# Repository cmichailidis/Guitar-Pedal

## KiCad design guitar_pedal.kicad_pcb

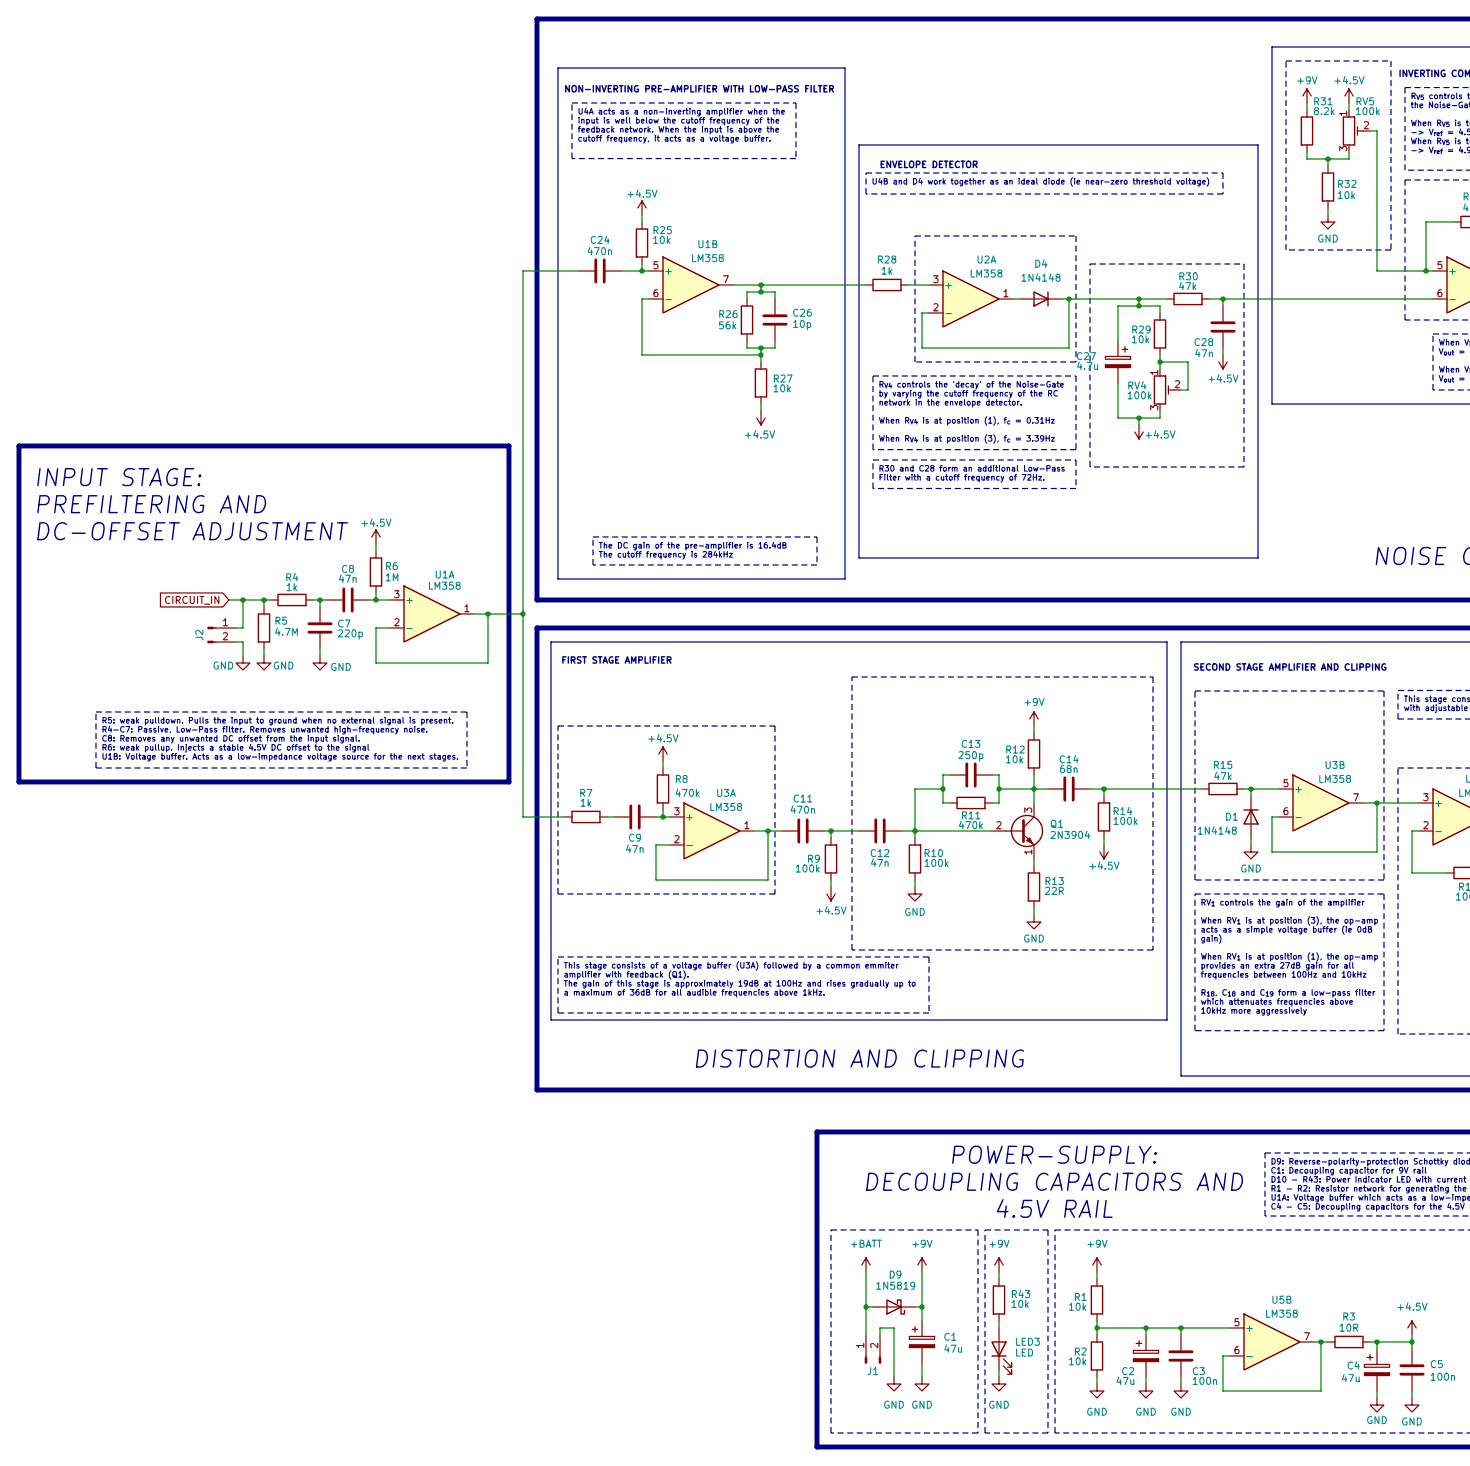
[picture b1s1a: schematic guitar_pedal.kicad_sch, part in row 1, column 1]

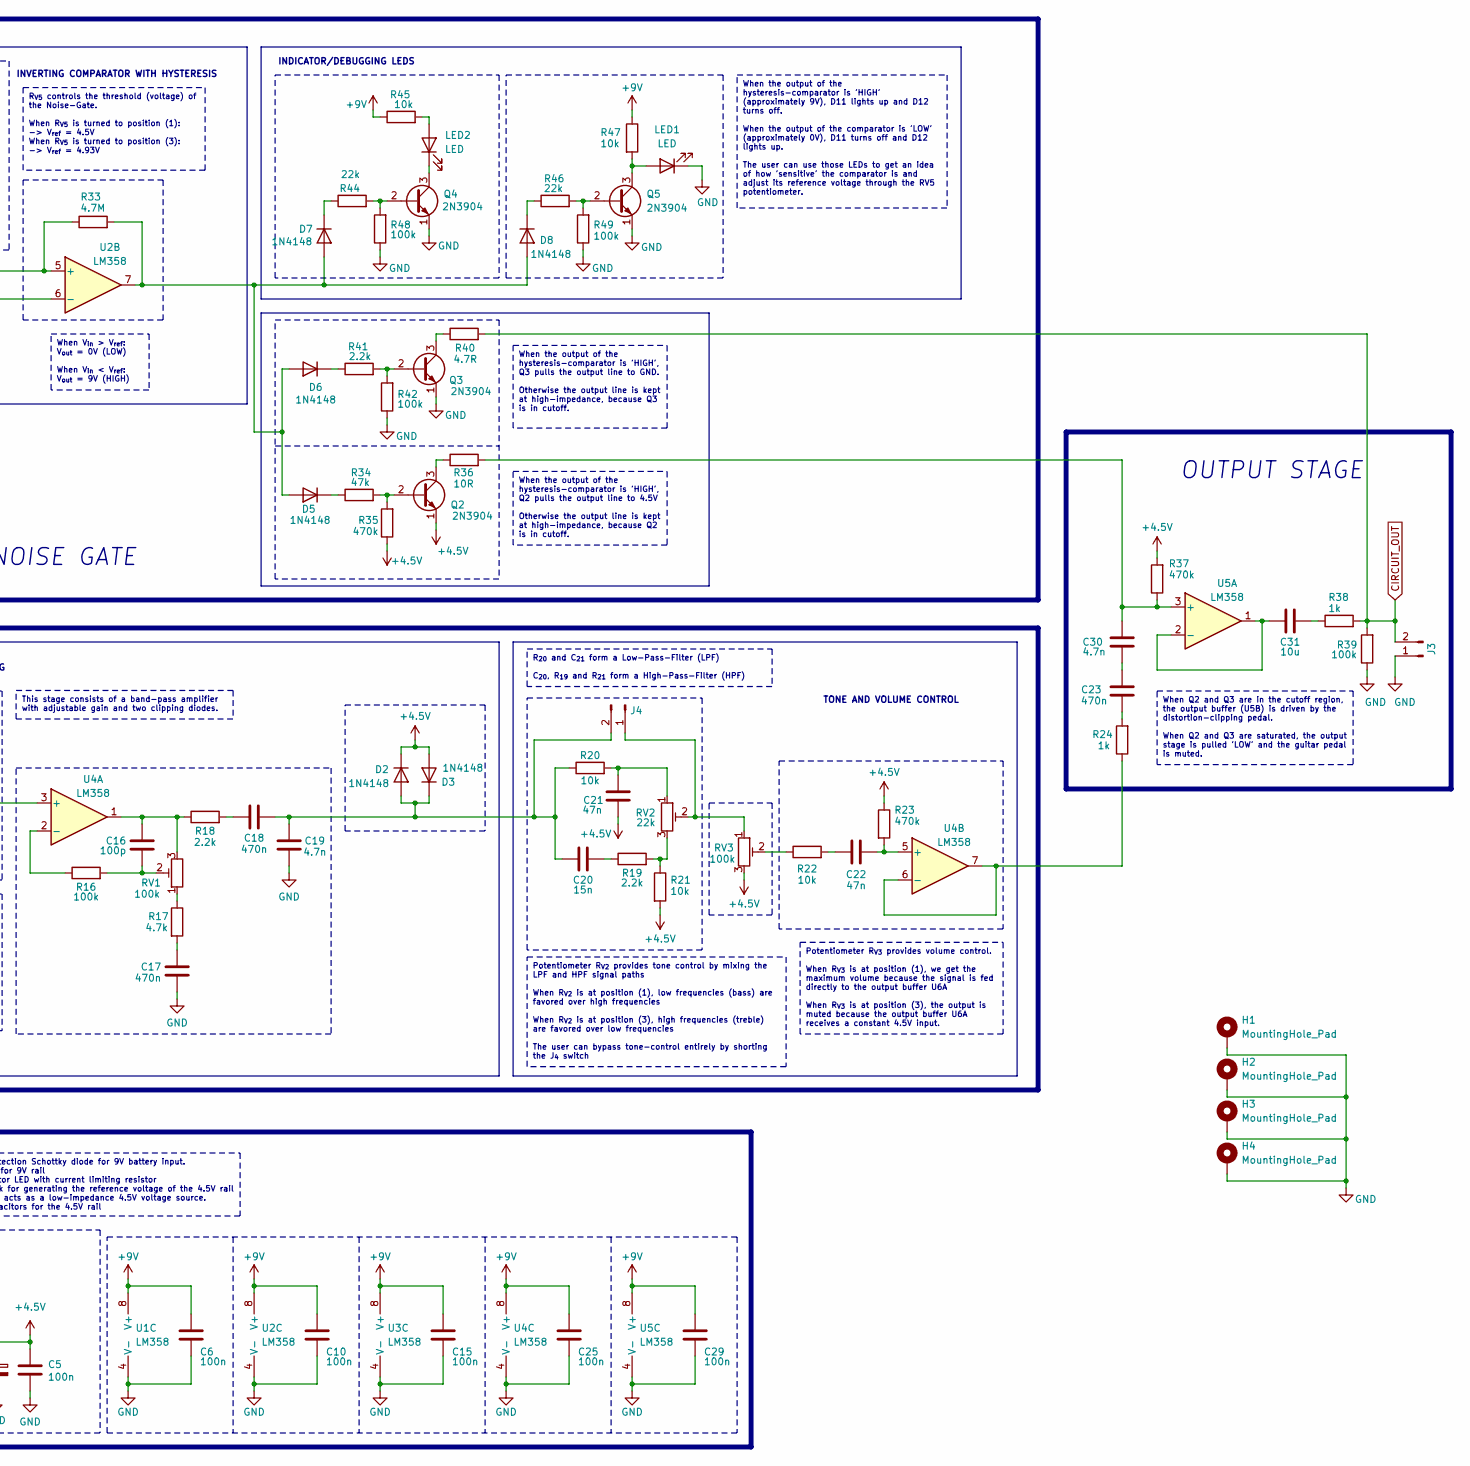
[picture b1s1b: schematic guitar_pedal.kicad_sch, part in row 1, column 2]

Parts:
C1, C2, C4: 47u; CP_Radial_D6.3mm_P2.50mm
C3, C5, C6, C10, C15, C25, C29: 100n; C_Rect_L7.2mm_W2.5mm_P5.00mm_FKS2_FKP2_MKS2_MKP2
C7: 220p; C_Disc_D6.0mm_W2.5mm_P5.00mm
C8, C9, C12, C21, C22, C28: 47n; C_Rect_L7.2mm_W2.5mm_P5.00mm_FKS2_FKP2_MKS2_MKP2
C11, C17, C18, C23, C24: 470n; C_Rect_L7.2mm_W3.5mm_P5.00mm_FKS2_FKP2_MKS2_MKP2
C13: 250p; C_Disc_D6.0mm_W2.5mm_P5.00mm
C14: 68n; C_Rect_L7.2mm_W2.5mm_P5.00mm_FKS2_FKP2_MKS2_MKP2
C16: 100p; C_Disc_D6.0mm_W2.5mm_P5.00mm
C19, C30: 4.7n; C_Rect_L7.2mm_W2.5mm_P5.00mm_FKS2_FKP2_MKS2_MKP2
C20: 15n; C_Rect_L7.2mm_W2.5mm_P5.00mm_FKS2_FKP2_MKS2_MKP2
C26: 10p; C_Disc_D6.0mm_W2.5mm_P5.00mm
C27: 4.7u; CP_Radial_D5.0mm_P2.50mm
C31: 10u; C_Disc_D6.0mm_W2.5mm_P5.00mm
D1, D2, D3, D4, D5, D6, D7, D8: 1N4148; D_DO-35_SOD27_P7.62mm_Horizontal
D9: 1N5819; D_DO-41_SOD81_P10.16mm_Horizontal
H1, H2, H3, H4: MountingHole_Pad; MountingHole_3.2mm_M3_DIN965_Pad
J1, J2, J3, J4: Conn_01x02_Pin; PinHeader_1x02_P2.54mm_Vertical
LED1, LED2, LED3: LED; PinHeader_1x02_P2.54mm_Vertical
Q1, Q2, Q3, Q4, Q5: 2N3904; TO-92_Inline
R1, R2, R12, R20, R21, R22, R25, R27, R29, R32, R43, R45, R47: 10k; R_Axial_DIN0207_L6.3mm_D2.5mm_P7.62mm_Horizontal
R3, R36: 10R; R_Axial_DIN0207_L6.3mm_D2.5mm_P7.62mm_Horizontal
R4, R7, R24, R28, R38: 1k; R_Axial_DIN0207_L6.3mm_D2.5mm_P7.62mm_Horizontal
R5, R33: 4.7M; R_Axial_DIN0207_L6.3mm_D2.5mm_P7.62mm_Horizontal
R6: 1M; R_Axial_DIN0207_L6.3mm_D2.5mm_P7.62mm_Horizontal
R8, R11, R23, R35, R37: 470k; R_Axial_DIN0207_L6.3mm_D2.5mm_P7.62mm_Horizontal
R9, R10, R14, R16, R39, R42, R48, R49: 100k; R_Axial_DIN0207_L6.3mm_D2.5mm_P7.62mm_Horizontal
R13: 22R; R_Axial_DIN0207_L6.3mm_D2.5mm_P7.62mm_Horizontal
R15, R30, R34: 47k; R_Axial_DIN0207_L6.3mm_D2.5mm_P7.62mm_Horizontal
R17: 4.7k; R_Axial_DIN0207_L6.3mm_D2.5mm_P7.62mm_Horizontal
R18, R19, R41: 2.2k; R_Axial_DIN0207_L6.3mm_D2.5mm_P7.62mm_Horizontal
R26: 56k; R_Axial_DIN0207_L6.3mm_D2.5mm_P7.62mm_Horizontal
R31: 8.2k; R_Axial_DIN0207_L6.3mm_D2.5mm_P7.62mm_Horizontal
R40: 4.7R; R_Axial_DIN0207_L6.3mm_D2.5mm_P7.62mm_Horizontal
R44, R46: 22k; R_Axial_DIN0207_L6.3mm_D2.5mm_P7.62mm_Horizontal
RV1, RV3, RV4, RV5: 100k; PinHeader_1x03_P2.54mm_Vertical
RV2: 22k; PinHeader_1x03_P2.54mm_Vertical
U1, U2, U3, U4, U5: LM358; DIP-8_W7.62mm

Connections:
+4.5V: C4.1, C5.2, C21.1, C27.2, C28.1, D2.1 (K), D3.2 (A), Q2.1 (E), R3.2, R6.1, R8.1, R9.1, R14.1, R21.2, R23.1, R25.1, R27.2, R35.1, R37.2, RV3.3, RV4.3, RV5.1
+9V: C1.1, C6.2, C10.2, C15.2, C25.2, C29.2, D9.1 (K), R1.1, R12.1, R31.1, R43.1, R45.1, R47.1, U1.8 (V+), U2.8 (V+), U3.8 (V+), U4.8 (V+), U5.8 (V+)
+BATT: D9.2 (A), J1.1
CIRCUIT_IN: J2.1, R4.1, R5.1
CIRCUIT_OUT: J3.2, R38.2, R39.2, R40.2
GND: C1.2, C2.2, C3.1, C4.2, C5.1, C6.1, C7.1, C10.1, C15.1, C17.1, C19.1, C25.1, C29.1, D1.2 (A), H1.1 (1_1), H2.1 (1_1), H3.1 (1_1), H4.1 (1_1), J1.2, J2.2, J3.1, LED1.1 (K), LED3.1 (K), Q3.1 (E), Q4.1 (E), Q5.1 (E), R2.2, R5.2, R10.1, R13.2, R32.2, R39.1, R42.1, R48.1, R49.1, U1.4 (V-), U2.4 (V-), U3.4 (V-), U4.4 (V-), U5.4 (V-)
unnamed: C7.2, C8.1, R4.2
unnamed: C9.1, R7.2
unnamed: C11.2, C12.2, R9.2
unnamed: C14.2, R14.2, R15.1
unnamed: C16.1, R16.2, RV1.2
unnamed: C16.2, R18.1, RV1.3, U4.1
unnamed: C17.2, R17.2
unnamed: C18.1, R18.2
unnamed: C20.2, R19.1
unnamed: C21.2, R20.2, RV2.1
unnamed: C22.1, R22.2
unnamed: C23.1, R24.2
unnamed: C23.2, C30.1
unnamed: C26.2, R26.1, R28.1, U1.7
unnamed: C31.2, R38.1
unnamed: D1.1 (K), R15.2, U3.5 (+)
unnamed: C18.2, C19.2, C20.1, D2.2 (A), D3.1 (K), J4.2, R20.1
unnamed: D4.2 (A), U2.1
unnamed: C27.1, D4.1 (K), R29.1, R30.1, U2.2 (-)
unnamed: D5.2 (A), D6.2 (A), D7.2 (A), D8.2 (A), R33.2, U2.7
unnamed: D5.1 (K), R34.1
unnamed: D6.1 (K), R41.1
unnamed: D7.1 (K), R44.1
unnamed: D8.1 (K), R46.1
unnamed: J4.1, RV2.2, RV3.1
unnamed: LED1.2 (A), Q5.3 (C), R47.2
unnamed: LED2.2 (A), R45.2
unnamed: LED2.1 (K), Q4.3 (C)
unnamed: LED3.2 (A), R43.2
unnamed: C12.1, C13.1, Q1.2 (B), R10.2, R11.1
unnamed: C13.2, C14.1, Q1.3 (C), R11.2, R12.2
unnamed: Q1.1 (E), R13.1
unnamed: Q2.2 (B), R34.2, R35.2
unnamed: Q2.3 (C), R36.1
unnamed: Q3.2 (B), R41.2, R42.2
unnamed: Q3.3 (C), R40.1
unnamed: Q4.2 (B), R44.2, R48.2
unnamed: Q5.2 (B), R46.2, R49.2
unnamed: R17.1, RV1.1
unnamed: R19.2, R21.1, RV2.3
unnamed: R22.1, RV3.2
unnamed: R29.2, RV4.1, RV4.2
unnamed: R31.2, R32.1, RV5.3
unnamed: C8.2, R6.2, U1.3 (+)
unnamed: C24.1, R7.1, U1.1, U1.2 (-)
unnamed: C24.2, R25.2, U1.5 (+)
unnamed: C26.1, R26.2, R27.1, U1.6 (-)
unnamed: R28.2, U2.3 (+)
unnamed: R33.1, RV5.2, U2.5 (+)
unnamed: C28.2, R30.2, U2.6 (-)
unnamed: C9.2, R8.2, U3.3 (+)
unnamed: C11.1, U3.1, U3.2 (-)
unnamed: U3.6 (-), U3.7, U4.3 (+)
unnamed: R16.1, U4.2 (-)
unnamed: C22.2, R23.2, U4.5 (+)
unnamed: R24.1, U4.6 (-), U4.7
unnamed: C30.2, R36.2, R37.1, U5.3 (+)
unnamed: C31.1, U5.1, U5.2 (-)
unnamed: C2.1, C3.2, R1.2, R2.1, U5.5 (+)
unnamed: R3.1, U5.6 (-), U5.7

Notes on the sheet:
SECOND STAGE AMPLIFIER AND CLIPPING
POWER-SUPPLY: DECOUPLING CAPACITORS AND 4.5V RAIL
INPUT STAGE: PREFILTERING AND DC-OFFSET ADJUSTMENT
NON-INVERTING PRE-AMPLIFIER WITH LOW-PASS FILTER
NOISE GATE
INVERTING COMPARATOR WITH HYSTERESIS
ENVELOPE DETECTOR
INDICATOR/DEBUGGING LEDS
DISTORTION AND CLIPPING
TONE AND VOLUME CONTROL
OUTPUT STAGE
FIRST STAGE AMPLIFIER
This stage consists of a voltage buffer (U3A) followed by a common emmiter amplifier with feedback (Q1). The gain of this stage is approximately 19dB at 100Hz and rises gradually up to a maximum of 36dB for all audible frequencies above 1kHz.
D9: Reverse-polarity-protection Schottky diode for 9V battery input. C1: Decoupling capacitor for 9V rail D10 - R43: Power Indicator LED with current limiting resistor R1 - R2: Resistor network for generating the reference voltage of the 4.5V rail U1A: Voltage buffer which acts as a low-impedance 4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
Potentiometer R_{V2} provides tone control by mixing the LPF and HPF signal paths When R_{V2} is at position (1), low frequencies (bass) are favored over high frequencies When R_{V2} is at position (3), high frequencies (treble) are favored over low frequencies The user can bypass tone-control enti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
When V_{in} > V_{ref}: V_{out} = 0V (LOW) When V_{in} < V_{ref}: V_{out} = 9V (HIGH)
The DC gain of the pre-amplifier is 16.4dB The cutoff frequency is 284kHz
RV_{1} controls the gain of the amplifier When RV_{1} is at position (3), the op-amp acts as a simple voltage buffer (ie 0dB gain) When RV_{1} is at position (1), the op-amp provides an extra 27dB gain for all frequencies between 100Hz and 10kHz R_{18}, C_{18} and C_{19} form a low-pass filter whic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
When the output of the hysteresis-comparator is 'HIGH', Q3 pulls the output line to GND. Otherwise the output line is kept at high-impedance, because Q3 is in cutoff.
U4B and D4 work together as an ideal diode (ie near-zero threshold voltage)
R5: weak pulldown. Pulls the input to ground when no external signal is present. R4-C7: Passive, Low-Pass filter. Removes unwanted high-frequency noise. C8: Removes any unwanted DC offset from the input signal. R6: weak pullup. Injects a stable 4.5V DC offset to the signal U1B: Voltage buffer. Acts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
R_{V5} controls the threshold (voltage) of the Noise-Gate. When R_{V5} is turned to position (1): -> V_{ref} = 4.5V When R_{V5} is turned to position (3): -> V_{ref} = 4.93V
When the output of the hysteresis-comparator is 'HIGH' (approximately 9V), D11 lights up and D12 turns off. When the output of the comparator is 'LOW' (approximately 0V), D11 turns off and D12 lights up. The user can use those LEDs to get an idea of how 'sensitive' the comparator is and adjust its 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
This stage consists of a band-pass amplifier with adjustable gain and two clipping diodes.
When the output of the hysteresis-comparator is 'HIGH', Q2 pulls the output line to 4.5V Otherwise the output line is kept at high-impedance, because Q2 is in cutoff.
R30 and C28 form an additional Low-Pass Filter with a cutoff frequency of 72Hz.
R_{20} and C_{21} form a Low-Pass-Filter (LPF) C_{20}, R_{19} and R_{21} form a High-Pass-Filter (HPF)
When Q2 and Q3 are in the cutoff region, the output buffer (U5B) is driven by the distortion-clipping pedal. When Q2 and Q3 are saturated, the output stage is pulled 'LOW' and the guitar pedal is muted.
R_{V4} controls the 'decay' of the Noise-Gate by varying the cutoff frequency of the RC network in the envelope detector. When R_{V4} is at position (1), f_{c} = 0.31Hz When R_{V4} is at position (3), f_{c} = 3.39Hz
Potentiometer R_{V3} provides volume control. When R_{V3} is at position (1), we get the maximum volume because the signal is fed directly to the output buffer U6A When R_{V3} is at position (3), the output is muted because the output buffer U6A receives a constant 4.5V input.
U4A acts as a non-inverting amplifier when the input is well below the cutoff frequency of the feedback network. When the input is above the cutoff frequency, it acts as a voltage buffer.

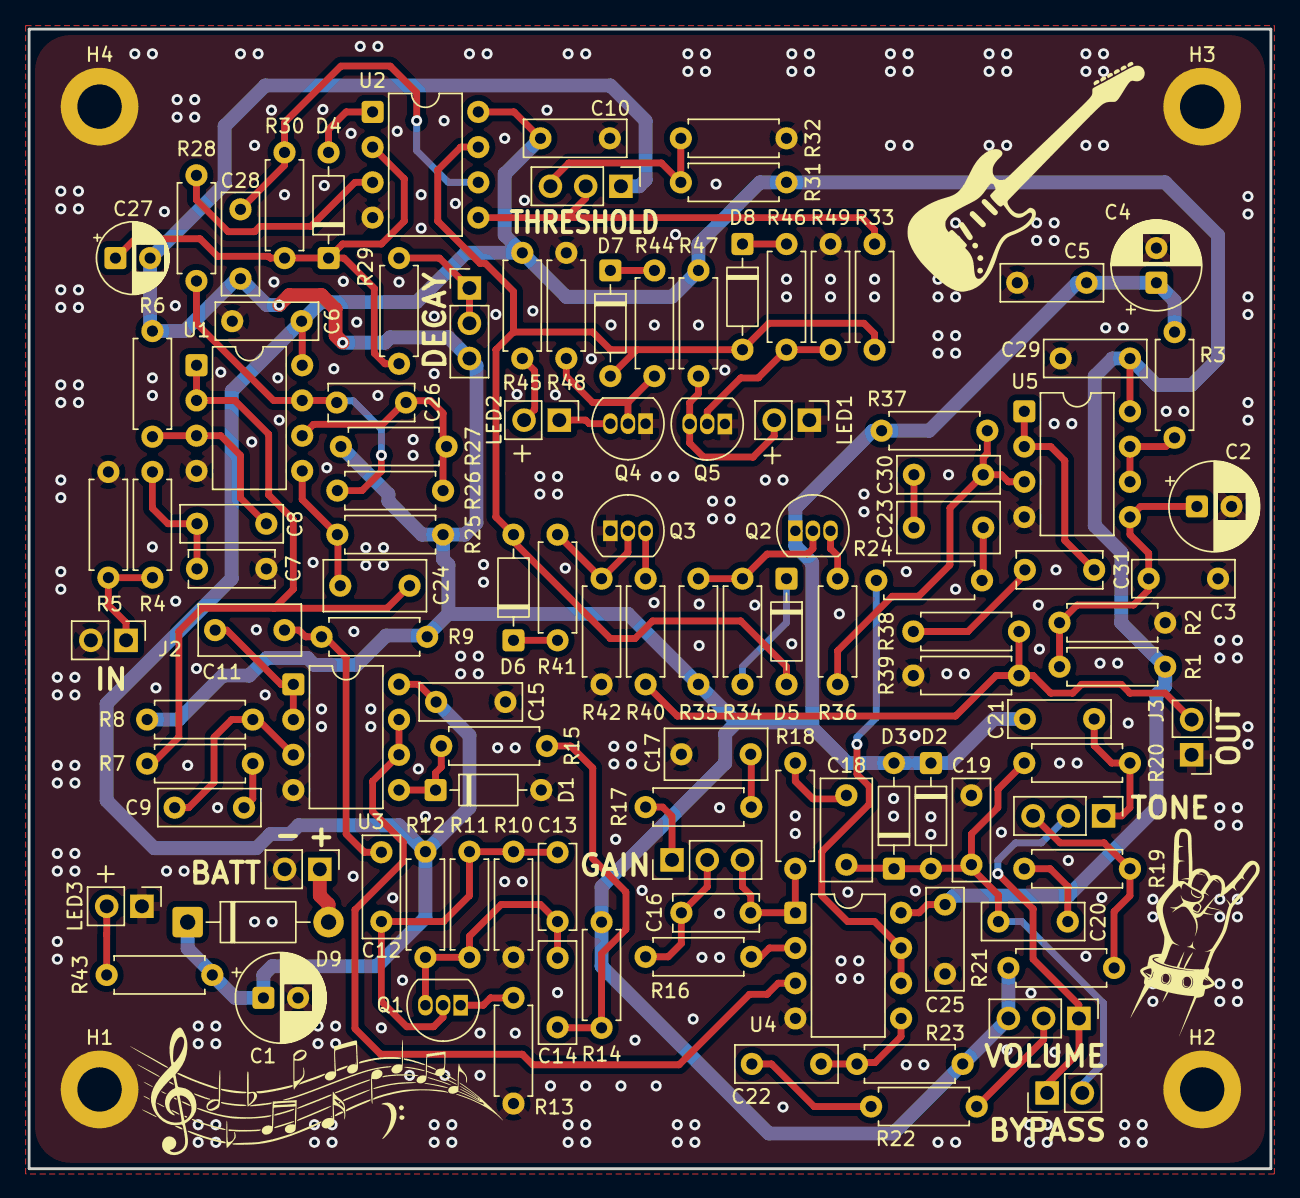
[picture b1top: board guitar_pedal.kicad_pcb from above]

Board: 2 copper layers, 89.5 x 82.2 mm, 115 parts (0 on the bottom side), 66 nets.

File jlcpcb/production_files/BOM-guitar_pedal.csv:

Comment,Designator,Footprint,LCSC,Quantity
4.7R,R40,R_Axial_DIN0207_L6.3mm_D2.5mm_P7.62mm_Horizontal,,1
47n,C21,C_Rect_L7.2mm_W2.5mm_P5.00mm_FKS2_FKP2_MKS2_MKP2,,1
2.2k,R19,R_Axial_DIN0207_L6.3mm_D2.5mm_P7.62mm_Horizontal,,1
470n,C17,C_Rect_L7.2mm_W3.5mm_P5.00mm_FKS2_FKP2_MKS2_MKP2,,1
100p,C16,C_Disc_D6.0mm_W2.5mm_P5.00mm,,1
470k,R11,R_Axial_DIN0207_L6.3mm_D2.5mm_P7.62mm_Horizontal,,1
470k,R37,R_Axial_DIN0207_L6.3mm_D2.5mm_P7.62mm_Horizontal,,1
2N3904,Q1,TO-92_Inline,,1
1N4148,D6,D_DO-35_SOD27_P7.62mm_Horizontal,,1
100n,C6,C_Rect_L7.2mm_W2.5mm_P5.00mm_FKS2_FKP2_MKS2_MKP2,,1
2.2k,R41,R_Axial_DIN0207_L6.3mm_D2.5mm_P7.62mm_Horizontal,,1
10k,R32,R_Axial_DIN0207_L6.3mm_D2.5mm_P7.62mm_Horizontal,,1
470k,R35,R_Axial_DIN0207_L6.3mm_D2.5mm_P7.62mm_Horizontal,,1
470n,C18,C_Rect_L7.2mm_W3.5mm_P5.00mm_FKS2_FKP2_MKS2_MKP2,,1
8.2k,R31,R_Axial_DIN0207_L6.3mm_D2.5mm_P7.62mm_Horizontal,,1
2.2k,R43,R_Axial_DIN0207_L6.3mm_D2.5mm_P7.62mm_Horizontal,,1
470n,C11,C_Rect_L7.2mm_W3.5mm_P5.00mm_FKS2_FKP2_MKS2_MKP2,,1
1M,R6,R_Axial_DIN0207_L6.3mm_D2.5mm_P7.62mm_Horizontal,,1
2N3904,Q5,TO-92_Inline,,1
1k,R24,R_Axial_DIN0207_L6.3mm_D2.5mm_P7.62mm_Horizontal,,1
Conn_01x02_Pin,J1,PinHeader_1x02_P2.54mm_Vertical,,1
47n,C8,C_Rect_L7.2mm_W2.5mm_P5.00mm_FKS2_FKP2_MKS2_MKP2,,1
47u,C2,CP_Radial_D6.3mm_P2.50mm,,1
2N3904,Q3,TO-92_Inline,,1
470k,R23,R_Axial_DIN0207_L6.3mm_D2.5mm_P7.62mm_Horizontal,,1
4.7M,R33,R_Axial_DIN0207_L6.3mm_D2.5mm_P7.62mm_Horizontal,,1
1k,R4,R_Axial_DIN0207_L6.3mm_D2.5mm_P7.62mm_Horizontal,,1
100R,R36,R_Axial_DIN0207_L6.3mm_D2.5mm_P7.62mm_Horizontal,,1
100k,R48,R_Axial_DIN0207_L6.3mm_D2.5mm_P7.62mm_Horizontal,,1
22k,R46,R_Axial_DIN0207_L6.3mm_D2.5mm_P7.62mm_Horizontal,,1
250p,C13,C_Disc_D6.0mm_W2.5mm_P5.00mm,,1
10p,C26,C_Disc_D6.0mm_W2.5mm_P5.00mm,,1
100n,C5,C_Rect_L7.2mm_W2.5mm_P5.00mm_FKS2_FKP2_MKS2_MKP2,,1
220p,C7,C_Disc_D6.0mm_W2.5mm_P5.00mm,,1
47k,R15,R_Axial_DIN0207_L6.3mm_D2.5mm_P7.62mm_Horizontal,,1
1N4148,D1,D_DO-35_SOD27_P7.62mm_Horizontal,,1
10k,R38,R_Axial_DIN0207_L6.3mm_D2.5mm_P7.62mm_Horizontal,,1
10k,R25,R_Axial_DIN0207_L6.3mm_D2.5mm_P7.62mm_Horizontal,,1
100k,R49,R_Axial_DIN0207_L6.3mm_D2.5mm_P7.62mm_Horizontal,,1
100k,R16,R_Axial_DIN0207_L6.3mm_D2.5mm_P7.62mm_Horizontal,,1
47n,C12,C_Rect_L7.2mm_W2.5mm_P5.00mm_FKS2_FKP2_MKS2_MKP2,,1
100k,RV4,PinHeader_1x03_P2.54mm_Vertical,,1
4.7n,C30,C_Rect_L7.2mm_W2.5mm_P5.00mm_FKS2_FKP2_MKS2_MKP2,,1
470n,C24,C_Rect_L7.2mm_W3.5mm_P5.00mm_FKS2_FKP2_MKS2_MKP2,,1
100n,C10,C_Rect_L7.2mm_W2.5mm_P5.00mm_FKS2_FKP2_MKS2_MKP2,,1
10k,R1,R_Axial_DIN0207_L6.3mm_D2.5mm_P7.62mm_Horizontal,,1
10u,C31,C_Disc_D6.0mm_W2.5mm_P5.00mm,,1
LM358,U4,DIP-8_W7.62mm,,1
1N5819,D9,D_DO-41_SOD81_P10.16mm_Horizontal,,1
LM358,U3,DIP-8_W7.62mm,,1
1k,R28,R_Axial_DIN0207_L6.3mm_D2.5mm_P7.62mm_Horizontal,,1
100n,C15,C_Rect_L7.2mm_W2.5mm_P5.00mm_FKS2_FKP2_MKS2_MKP2,,1
15n,C20,C_Rect_L7.2mm_W2.5mm_P5.00mm_FKS2_FKP2_MKS2_MKP2,,1
1N4148,D4,D_DO-35_SOD27_P7.62mm_Horizontal,,1
10k,R2,R_Axial_DIN0207_L6.3mm_D2.5mm_P7.62mm_Horizontal,,1
LM358,U2,DIP-8_W7.62mm,,1
47n,C28,C_Rect_L7.2mm_W2.5mm_P5.00mm_FKS2_FKP2_MKS2_MKP2,,1
47k,R34,R_Axial_DIN0207_L6.3mm_D2.5mm_P7.62mm_Horizontal,,1
10k,R27,R_Axial_DIN0207_L6.3mm_D2.5mm_P7.62mm_Horizontal,,1
2.2k,R18,R_Axial_DIN0207_L6.3mm_D2.5mm_P7.62mm_Horizontal,,1
10k,R12,R_Axial_DIN0207_L6.3mm_D2.5mm_P7.62mm_Horizontal,,1
100k,R39,R_Axial_DIN0207_L6.3mm_D2.5mm_P7.62mm_Horizontal,,1
1k,R7,R_Axial_DIN0207_L6.3mm_D2.5mm_P7.62mm_Horizontal,,1
100k,R9,R_Axial_DIN0207_L6.3mm_D2.5mm_P7.62mm_Horizontal,,1
22k,RV2,PinHeader_1x03_P2.54mm_Vertical,,1
100k,RV1,PinHeader_1x03_P2.54mm_Vertical,,1
10k,R29,R_Axial_DIN0207_L6.3mm_D2.5mm_P7.62mm_Horizontal,,1
Conn_01x02_Pin,J3,PinHeader_1x02_P2.54mm_Vertical,,1
4.7u,C27,CP_Radial_D5.0mm_P2.50mm,,1
1N4148,D8,D_DO-35_SOD27_P7.62mm_Horizontal,,1
10k,R21,R_Axial_DIN0207_L6.3mm_D2.5mm_P7.62mm_Horizontal,,1
470k,R8,R_Axial_DIN0207_L6.3mm_D2.5mm_P7.62mm_Horizontal,,1
LM358,U1,DIP-8_W7.62mm,,1
10k,R22,R_Axial_DIN0207_L6.3mm_D2.5mm_P7.62mm_Horizontal,,1
470n,C23,C_Rect_L7.2mm_W3.5mm_P5.00mm_FKS2_FKP2_MKS2_MKP2,,1
100k,RV5,PinHeader_1x03_P2.54mm_Vertical,,1
1N4148,D5,D_DO-35_SOD27_P7.62mm_Horizontal,,1
56k,R26,R_Axial_DIN0207_L6.3mm_D2.5mm_P7.62mm_Horizontal,,1
100k,R42,R_Axial_DIN0207_L6.3mm_D2.5mm_P7.62mm_Horizontal,,1
10k,R20,R_Axial_DIN0207_L6.3mm_D2.5mm_P7.62mm_Horizontal,,1
4.7k,R17,R_Axial_DIN0207_L6.3mm_D2.5mm_P7.62mm_Horizontal,,1
100n,C25,C_Rect_L7.2mm_W2.5mm_P5.00mm_FKS2_FKP2_MKS2_MKP2,,1
1N4148,D3,D_DO-35_SOD27_P7.62mm_Horizontal,,1
Conn_01x02_Pin,J2,PinHeader_1x02_P2.54mm_Vertical,,1
2.2k,R47,R_Axial_DIN0207_L6.3mm_D2.5mm_P7.62mm_Horizontal,,1
100n,C29,C_Rect_L7.2mm_W2.5mm_P5.00mm_FKS2_FKP2_MKS2_MKP2,,1
100k,RV3,PinHeader_1x03_P2.54mm_Vertical,,1
100k,R10,R_Axial_DIN0207_L6.3mm_D2.5mm_P7.62mm_Horizontal,,1
2N3904,Q4,TO-92_Inline,,1
LM358,U5,DIP-8_W7.62mm,,1
2.2k,R45,R_Axial_DIN0207_L6.3mm_D2.5mm_P7.62mm_Horizontal,,1
47n,C9,C_Rect_L7.2mm_W2.5mm_P5.00mm_FKS2_FKP2_MKS2_MKP2,,1
4.7M,R5,R_Axial_DIN0207_L6.3mm_D2.5mm_P7.62mm_Horizontal,,1
4.7n,C19,C_Rect_L7.2mm_W2.5mm_P5.00mm_FKS2_FKP2_MKS2_MKP2,,1
47u,C4,CP_Radial_D6.3mm_P2.50mm,,1
22k,R44,R_Axial_DIN0207_L6.3mm_D2.5mm_P7.62mm_Horizontal,,1
47n,C22,C_Rect_L7.2mm_W2.5mm_P5.00mm_FKS2_FKP2_MKS2_MKP2,,1
47k,R30,R_Axial_DIN0207_L6.3mm_D2.5mm_P7.62mm_Horizontal,,1
68n,C14,C_Rect_L7.2mm_W2.5mm_P5.00mm_FKS2_FKP2_MKS2_MKP2,,1
1N4148,D2,D_DO-35_SOD27_P7.62mm_Horizontal,,1
1N4148,D7,D_DO-35_SOD27_P7.62mm_Horizontal,,1
10R,R3,R_Axial_DIN0207_L6.3mm_D2.5mm_P7.62mm_Horizontal,,1
47u,C1,CP_Radial_D6.3mm_P2.50mm,,1
100k,R14,R_Axial_DIN0207_L6.3mm_D2.5mm_P7.62mm_Horizontal,,1
2N3904,Q2,TO-92_Inline,,1
100n,C3,C_Rect_L7.2mm_W2.5mm_P5.00mm_FKS2_FKP2_MKS2_MKP2,,1
22R,R13,R_Axial_DIN0207_L6.3mm_D2.5mm_P7.62mm_Horizontal,,1
LED,LED3,PinHeader_1x02_P2.54mm_Vertical,,1
Conn_01x02_Pin,J4,PinHeader_1x02_P2.54mm_Vertical,,1
LED,LED1,PinHeader_1x02_P2.54mm_Vertical,,1
LED,LED2,PinHeader_1x02_P2.54mm_Vertical,,1
